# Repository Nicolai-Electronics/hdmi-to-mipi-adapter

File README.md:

# HDMI to MIPI adapter board

This board design is a work in progress, use at your own risk.

## License

License: CERN-OHL-P

Copyright Nicolai Electronics 2024

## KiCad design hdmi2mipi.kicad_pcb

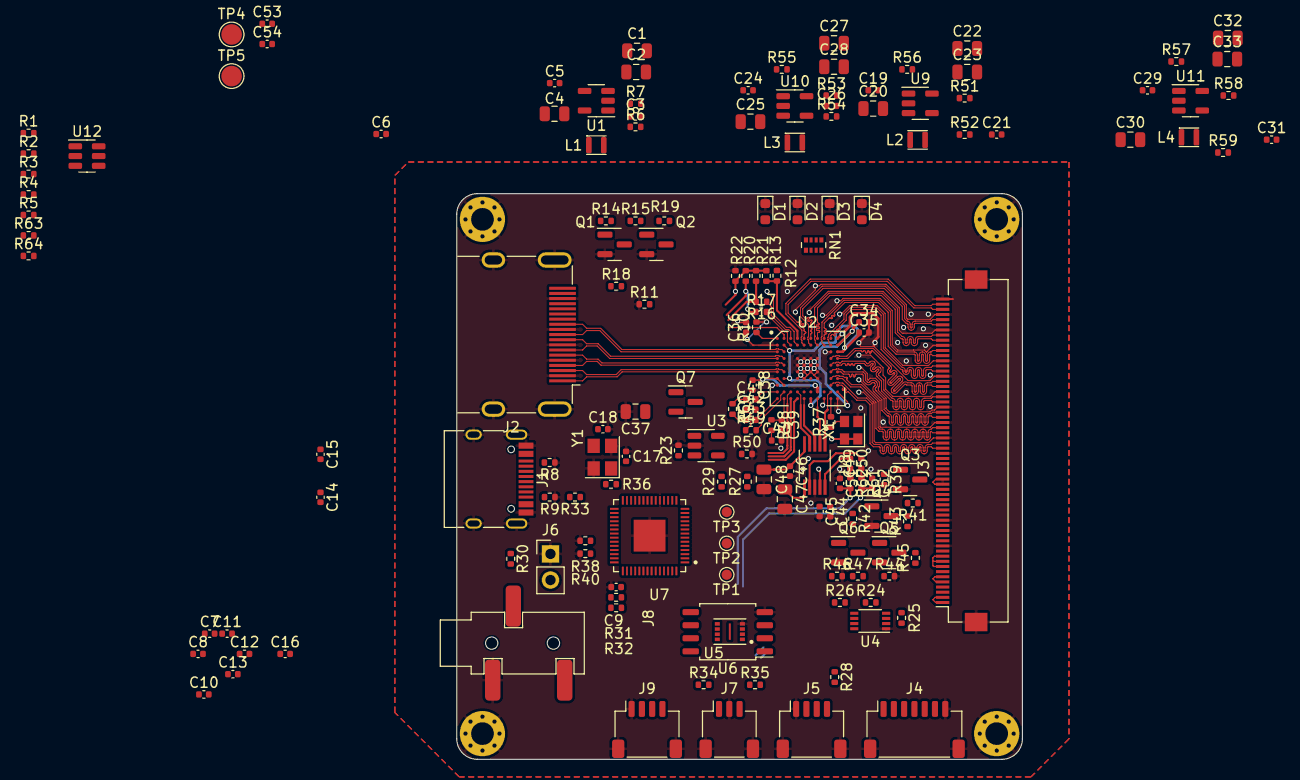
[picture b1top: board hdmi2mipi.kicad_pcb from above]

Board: 4 copper layers, 55.0 x 55.0 mm, 166 parts (0 on the bottom side), 140 nets.

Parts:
C1, C2, C4, C20, C22, C23, C25, C27, C28, C30, C32, C33, C37: 22u; C_0805_2012Metric
C3, C17, C18, C21, C26, C31: 22p; C_0402_1005Metric
C5, C7, C9, C10, C12, C13, C14, C15, C16, C19, C24, C29, C34, C35, C36, C38, C45, C46, C49, C50: 100n; C_0402_1005Metric
C6, C54: C_0402_1005Metric
C8, C11, C44: 1u; C_0402_1005Metric
C39, C43: 1n; C_0402_1005Metric
C40, C41: 0.1u; C_0402_1005Metric
C42: 5p; C_0402_1005Metric
C47, C48: 47u; C_0805_2012Metric
C51, C52: 39n; C_0402_1005Metric
C53: 2.2u; C_0402_1005Metric
D1, D2, D3, D4: LED; LED_0603_1608Metric
H1, H2, H3, H4: MountingHole_Pad; MountingHole_2.2mm_M2_Pad_Via
J1: USB_C_Receptacle_USB2.0; USB_C_Receptacle_HRO_TYPE-C-31-M-12
J2: HDMI_A_1.4; HDMI_A_Molex_208658-1001_Horizontal
J3: Hirose_FH52-60S-0.5SH_1x60-1MP_P0.50mm_Horizontal
J4: TP; JST_SH_SM07B-SRSS-TB_1x07-1MP_P1.00mm_Horizontal
J5, J9: QWIIC; JST_SH_SM04B-SRSS-TB_1x04-1MP_P1.00mm_Horizontal
J6: BOOT; PinHeader_1x02_P2.54mm_Vertical
J7: SWD; JST_SH_SM03B-SRSS-TB_1x03-1MP_P1.00mm_Horizontal
J8: AudioJack3; Boom-audiojack-PJ-320B
L1, L2, L3, L4: 2.2u; Inductor_MSC20FC
Q1, Q2, Q3, Q4, Q5, Q6: BC846; SOT-23
Q7: 2SC2712; SOT-23
R1, R7, R15, R38, R39, R40, R42, R44, R46, R50, R51, R52, R53, R55, R56, R57, R58: 10k; R_0402_1005Metric
R2, R12: 0; R_0402_1005Metric
R3, R4: 10; R_0402_1005Metric
R5: 6.8k; R_0402_1005Metric
R6: 45.3k; R_0402_1005Metric
R8, R9: 5.1k; R_0402_1005Metric
R10: 2k; R_0402_1005Metric
R11: 48k; R_0402_1005Metric
R13, R49: 1.5k; R_0402_1005Metric
R14, R20, R21, R23, R24, R25, R26, R27, R28, R29, R41, R43, R45, R47: 4.7k; R_0402_1005Metric
R16, R17, R37: 33; R_0402_1005Metric
R18, R19, R30, R33, R36, R48, R60: 1k; R_0402_1005Metric
R22, R64: 100k; R_0402_1005Metric
R31, R32: 27; R_0402_1005Metric
R34, R35: 100; R_0402_1005Metric
R54: 8.2k; R_0402_1005Metric
R59: 20k; R_0402_1005Metric
R61, R62: 330; R_0402_1005Metric
R63: 50k; R_0402_1005Metric
RN1: 1K; R_Array_Convex_4x0402
TP1, TP2, TP3: TestPoint; TestPoint_Pad_D1.0mm
TP4, TP5: TestPoint; TestPoint_Pad_D2.0mm
U1, U9, U10, U11: SY8079AAC; SOT-23-5
U2: tc358840xbg
U3: SY6280AAC; SOT-23-5
U4: PCA9306DC; VSSOP-8_2.3x2mm_P0.5mm
U5: W25Q16JVUXIQ; PSON50P300X200X60-9N
U6: W25Q16JVUXIQ; SOIC-8_5.23x5.23mm_P1.27mm
U7: RP2040; QFN40P700X700X90-57N
U8: MS4344; SOP50P490X110-10N
U12: SOT-23-6
X1: SG-210STF; Oscillator_SMD_SeikoEpson_SG210-4Pin_2.5x2.0mm
Y1: 12MHz; Crystal_SMD_3225-4Pin_3.2x2.5mm

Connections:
1V1_EN: R55.1, U7.18 (GPIO15), U10.1 (EN)
1V2_EN: R56.1, U7.27 (GPIO16), U9.1 (EN)
1V8_EN: R57.1, U7.28 (GPIO17), U11.1 (EN)
1V8_S1: Q6.1 (B), R46.1, U7.2 (GPIO0)
1V8_S2: Q5.1 (B), R44.1, U7.3 (GPIO1)
3V3_HDMI: C36.1, C37.1, C38.1, J3.24 (3.3v), J3.25 (3.3v), J4.6, Q7.3 (C), R10.2, R27.1, R29.1, R41.1, R43.1, U2.B1 (VDD33_HDMI), U2.G1 (VDD33_HDMI), U2.H2 (VDDIO33), U2.J7 (VDDIO18), U3.1 (OUT), X1.1 (~ST), X1.4 (Vcc)
3V3_S1: Q4.1 (B), R42.1, U7.4 (GPIO2)
3V3_S2: Q3.1 (B), R39.1, U7.5 (GPIO3)
+1V1: C26.1, C27.1, C28.1, C35.1, L3.1, R54.1, U2.B2 (VDD11_HDMI), U2.C10 (VDDC11), U2.G2 (VDD11_HDMI), U2.K6 (VDDC11)
+1V2: C21.1, C22.1, C23.1, C34.1, L2.1, R52.1, U2.B10 (VDD12_MIPI1), U2.J10 (VDD12_MIPI0)
+1V8: C31.1, C32.1, C33.1, J3.22 (1.8v), J4.5, L4.1, R24.1, R25.1, R45.1, R47.1, R59.1, U4.2 (VREF1)
+3V3: C1.1, C2.1, C3.1, C7.1, C11.1, C12.1, C13.1, C14.1, C15.1, C16.1, C44.1, C45.1, J5.2, J9.2, L1.1, R6.1, R26.1, R28.1, R33.2, U3.5 (IN), U4.7 (VREF2), U4.8 (EN), U5.8 (VDD), U6.8 (VDD), U7.1 (IOVDD), U7.10 (IOVDD), U7.22 (IOVDD), U7.33 (IOVDD), U7.42 (IOVDD), U7.43 (ADC_AVDD), U7.44 (VREG_VIN), U7.48 (USB_VDD), U7.49 (IOVDD), U8.9 (VA)
/AUDIO_L: C52.2, J8.T, R61.2
/AUDIO_R: C51.2, J8.R, R62.2
/DSI0_C_N: J3.38 (DSI0CN), U2.F9 (CDSI0CN)
/DSI0_C_P: J3.37 (DSI0CP), U2.F10 (CDSI0CP)
/DSI0_D0_N: J3.32 (DSI0D0N), U2.H9 (CDSI0D0N)
/DSI0_D0_P: J3.31 (DSI0D0P), U2.H10 (CDSI0D0P)
/DSI0_D1_N: J3.35 (DSI0D1N), U2.G9 (CDSI0D1N)
/DSI0_D1_P: J3.34 (DSI0D1P), U2.G10 (CDSI0D1P)
/DSI0_D2_N: J3.41 (DSI0D2N), U2.E9 (CDSI0D2N)
/DSI0_D2_P: J3.40 (DSI0D2P), U2.E10 (CDSI0D2P)
/DSI0_D3_N: J3.44 (DSI0D3N), U2.D9 (CDSI0D3N)
/DSI0_D3_P: J3.43 (DSI0D3P), U2.D10 (CDSI0D3P)
/DSI1_C_N: J3.53 (DSI1CN), U2.B7 (CDSI1CN)
/DSI1_C_P: J3.52 (DSI1CP), U2.A7 (CDSI1CP)
/DSI1_D0_N: J3.47 (DSI1D0N), U2.B9 (CDSI1D0N)
/DSI1_D0_P: J3.46 (DSI1D0P), U2.A9 (CDSI1D0P)
/DSI1_D1_N: J3.50 (DSID1N), U2.B8 (CDSI1D1N)
/DSI1_D1_P: J3.49 (DSID1P), U2.A8 (CDSI1D1P)
/DSI1_D2_N: J3.56 (DSI1D2N), U2.B6 (CDSI1D2N)
/DSI1_D2_P: J3.55 (DSI1D2P), U2.A6 (CDSI1D2P)
/DSI1_D3_N: J3.59 (DSI1D3N), U2.B5 (CDSI1D3N)
/DSI1_D3_P: J3.58 (DSI1D3P), U2.A5 (CDSI1D3P)
/FB11: C26.2, R53.1, R54.2, U10.5 (FB)
/FB12: C21.2, R51.1, R52.2, U9.5 (FB)
/FB18: C31.2, R58.1, R59.2, U11.5 (FB)
/FB33: C3.2, R6.2, R7.1, U1.5 (FB)
/HDMI_0_N: J2.9 (D0-), U2.D2 (HDMID0N)
/HDMI_0_P: J2.7 (D0+), U2.D1 (HDMID0P)
/HDMI_1_N: J2.6 (D1-), U2.E2 (HDMID1N)
/HDMI_1_P: J2.4 (D1+), U2.E1 (HDMID1P)
/HDMI_2_N: J2.3 (D2-), U2.F2 (HDMID2N)
/HDMI_2_P: J2.1 (D2+), U2.F1 (HDMID2P)
/HDMI_C_N: J2.12 (CK-), U2.C2 (HDMICN)
/HDMI_C_P: J2.10 (CK+), U2.C1 (HDMICP)
/RP_BTN: J6.2, R30.2
/RP_QSPI_CSN: R30.1, U5.1 (~CS), U6.1 (~CS), U7.56 (QSPI_CSN)
/RP_QSPI_SCLK: U5.6 (SCK), U6.6 (SCK), U7.52 (QSPI_SCLK)
/RP_QSPI_SD0: U5.5 (MOSI/IO0), U6.5 (MOSI/IO0), U7.53 (QSPI_SD0)
/RP_QSPI_SD1: U5.2 (MISO/IO1), U6.2 (MISO/IO1), U7.55 (QSPI_SD1)
/RP_QSPI_SD2: U5.3 (IO2), U6.3 (IO2), U7.54 (QSPI_SD2)
/RP_QSPI_SD3: U5.7 (IO3), U6.7 (IO3), U7.51 (QSPI_SD3)
/RP_XIN: C17.1, U7.20 (XIN), Y1.1
/RP_XOUT: R36.2, U7.21 (XOUT)
/SW11: L3.2, U10.3 (SW)
/SW12: L2.2, U9.3 (SW)
/SW18: L4.2, U11.3 (SW)
/SW33: L1.2, U1.3 (SW)
/rpi_1.1v: C8.1, C9.1, C10.1, U7.23 (DVDD), U7.45 (VREG_VOUT), U7.50 (DVDD)
BL_EN: R1.1, U7.29 (GPIO18), U12.4 (EN)
BL_PWM: R64.2, U7.30 (GPIO19)
GND: C1.2, C2.2, C4.2, C5.2, C6.2, C7.2, C8.2, C9.2, C10.2, C11.2, C12.2, C13.2, C14.2, C15.2, C16.2, C17.2, C18.2, C19.2, C20.2, C22.2, C23.2, C24.2, C25.2, C27.2, C28.2, C29.2, C30.2, C32.2, C33.2, C34.2, C35.2, C36.2, C37.2, C38.2, C39.2, C40.2, C44.2, C45.2, C46.2, C47.2, C48.2, C51.1, C52.1, C53.2, C54.2, D1.1 (K), D2.1 (K), D3.1 (K), D4.1 (K), H1.1, H2.1, H3.1, H4.1, J1.A1 (GND), J1.A12 (GND), J1.B1 (GND), J1.B12 (GND), J1.S1 (SHIELD), J2.2 (D2S), J2.5 (D1S), J2.8 (D0S), J2.11 (CKS), J2.17 (GND), J2.SH, J3.12 (GND), J3.15 (GND), J3.17 (GND), J3.30 (GND), J3.33 (GND), J3.36 (GND), J3.39 (GND), J3.42 (GND), J3.45 (GND), J3.48 (GND), J3.51 (GND), J3.54 (GND), J3.57 (GND), J3.60 (GND), J3.MP, J4.7, J4.MP (MountPin), J5.1, J5.MP (MountPin), J6.1, J7.2, J7.MP (MountPin), J8.S, J9.1, J9.MP (MountPin), Q1.2 (E), Q2.2 (E), Q3.2 (E), Q4.2 (E), Q5.2 (E), Q6.2 (E), R1.2, R2.1, R7.2, R8.1, R9.1, R11.1, R22.1, R23.2, R38.2, R39.2, R40.2, R42.2, R44.2, R46.2, R50.2, R51.2, R53.2, R55.2, R56.2, R57.2, R58.2, U1.2 (GND), U2.A10 (VSS), U2.C9 (VSS), U2.D4 (VSS), U2.D5 (VSS), U2.D6 (VSS), U2.D7 (VSS), U2.E4 (VSS), U2.E5 (VSS), U2.E6 (VSS), U2.E7 (VSS), U2.F4 (VSS), U2.F5 (VSS), U2.F6 (VSS), U2.F7 (VSS), U2.G4 (VSS), U2.G5 (TEST), U2.G7 (VSS), U2.H1 (VSS), U2.K10 (VSS), U3.2 (GND), U4.1 (GND), U5.4 (VSS), U6.4 (VSS), U7.19 (TESTEN), U7.57 (GND), U8.8 (GND), U9.2 (GND), U10.2 (GND), U11.2 (GND), U12.2 (GND), X1.2 (GND), Y1.2, Y1.4
unnamed: C6.1, R11.2, R13.2, R19.2
unnamed: C18.1, R36.1, Y1.3
unnamed: C40.1, R48.2
unnamed: C41.1, C42.2, R60.1
unnamed: C49.1, R61.1
unnamed: C50.2, R62.1
unnamed: C54.1, R63.2, R64.1
unnamed: D1.2 (A), RN1.4 (R4.1)
unnamed: D2.2 (A), RN1.3 (R3.1)
unnamed: D3.2 (A), RN1.2 (R2.1)
unnamed: D4.2 (A), RN1.1 (R1.1)
unnamed: C53.1, J3.8 (LED+), J3.9 (LED+), J3.10 (LED+), U12.5 (OVP)
unnamed: J1.A5 (CC1), R8.2
unnamed: J1.B5 (CC2), R9.2
unnamed: J1.A6 (D+), J1.B6 (D+), R32.2
unnamed: J1.A7 (D-), J1.B7 (D-), R31.1
unnamed: J2.18 (+5V), R12.1, R15.1, R20.1, R21.1, R22.2
unnamed: J2.13 (CEC), U2.A2 (CEC)
unnamed: J2.19 (HPD/HEAC-), Q2.3 (C), R18.2, R19.1
unnamed: J2.15 (SCL), R16.2, R21.2
unnamed: J2.16 (SDA), R17.1, R20.2
unnamed: J3.20 (1.8-S1), Q6.3 (C), R47.2
unnamed: J3.19 (1.8-S2), Q5.3 (C), R45.2
unnamed: J3.27 (3.3-S2), J3.28 (3.3-S1), Q3.3 (C), Q4.3 (C), R41.2, R43.2
unnamed: J3.14 (5.8v-VDD), TP5.1
unnamed: J3.13 (5.8v-VEE), TP4.1
unnamed: J3.1 (FB1), J3.2 (FB1), R2.2, R3.1, R4.1
unnamed: J3.5 (FB2), J3.6 (FB2), R3.2, R4.2, R5.1
unnamed: J4.3, R24.2, U4.3 (SCL1)
unnamed: J4.4, R25.2, U4.4 (SDA1)
unnamed: J5.3, R26.2, U4.5 (SDA2), U7.34 (GPIO22)
unnamed: J5.4, R28.2, U4.6 (SCL2), U7.35 (GPIO23)
unnamed: J7.1, R34.1
unnamed: J7.3, R35.1
unnamed: J9.3, R29.2, U2.K3 (I2C_SDA), U7.36 (GPIO24)
unnamed: J9.4, R27.2, U2.K4 (I2C_SCL), U7.37 (GPIO25)
unnamed: Q1.1 (B), R14.1
unnamed: Q1.3 (C), Q2.1 (B), R15.2
unnamed: C42.1, Q7.1 (B), R49.1
unnamed: C43.1, Q7.2 (E), R60.2
unnamed: RN1.8 (R1.2), U7.17 (GPIO14)
unnamed: RN1.7 (R2.2), U7.16 (GPIO13)
unnamed: RN1.6 (R3.2), U7.15 (GPIO12)
unnamed: RN1.5 (R4.2), U7.14 (GPIO11)
unnamed: U2.J4 (A_OSCK), U8.4 (MCLK)
unnamed: U2.K7 (A_SCK), U8.2 (~DEM/SCLK)
unnamed: U2.J9 (A_SD0), U8.1 (SDIN)
unnamed: U2.K5 (A_WFS), U8.3 (LRCK)
unnamed: C41.2, U2.J1 (BIASDA)
unnamed: R49.2, U2.J2 (DAOUT)
unnamed: R16.1, U2.A3 (DDC_SCL)
unnamed: R17.2, U2.B3 (DDC_SDA)
unnamed: R12.2, R13.1, U2.A4 (HPDI)
unnamed: R14.2, R18.1, U2.B4 (HPDO)
unnamed: R40.1, U2.J3 (INT), U7.40 (GPIO28/ADC2)
unnamed: C43.2, U2.K1 (PCKIN)
unnamed: C39.1, R48.1, U2.K2 (PFIL)
unnamed: R37.2, U2.K9 (REFCLK)
unnamed: R10.1, U2.A1 (REXT)
unnamed: R38.1, U2.K8 (~RESET), U7.39 (GPIO27/ADC1)
unnamed: R50.1, U3.4 (ON), U7.38 (GPIO26/ADC0)
unnamed: R23.1, U3.3 (SET)
unnamed: TP1.1, U7.6 (GPIO4)
unnamed: TP2.1, U7.7 (GPIO5)
unnamed: TP3.1, U7.8 (GPIO6)
unnamed: R33.1, U7.26 (RUN)
unnamed: R34.2, U7.24 (SWCLK)
unnamed: R35.2, U7.25 (SWD)
unnamed: R31.2, U7.46 (USB_DM)
unnamed: R32.1, U7.47 (USB_DP)
unnamed: C49.2, U8.7 (AOUTL)
unnamed: C50.1, U8.10 (AOUTR)
unnamed: C47.1, U8.6 (FILT+)
unnamed: C46.1, C48.1, U8.5 (VQ)
unnamed: R5.2, R63.1, U12.3 (FB)
unnamed: R37.1, X1.3 (OUT)
VBUS: C4.1, C5.1, C19.1, C20.1, C24.1, C25.1, C29.1, C30.1, J1.A4 (VBUS), J1.A9 (VBUS), J1.B4 (VBUS), J1.B9 (VBUS), U1.1 (EN), U1.4 (VIN), U9.4 (VIN), U10.4 (VIN), U11.4 (VIN), U12.6 (Vin)

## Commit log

2023-11-19 Symbol and footprint
2023-11-24 Add RP2040, fix pinout, add transistors for controlling the 1.8v and 3.3v outputs on the MIPI connector
2023-12-01 Most of schematic done, experimenting with component placement
2023-12-09 Board to 7cm+-
2024-01-05 Fix board outline and center circuit board on grid
2024-01-24 Backlight driver
2024-01-24 Fill more BOM entries
2024-02-14 Add readme
